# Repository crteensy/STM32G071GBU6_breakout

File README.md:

# STM32G071GBU6_breakout
Breakout board for the STM32G071GBU6

## Partially tested
I've built one of these and measured:

- (unpowered) no shorts
- (unpowered) diode between I/O and ground
- (powered) 3V3 output is fine

Reset was not tested.

I didn't have the exact switch (KMR2) but one with an extra ground tab (KMR2xxG) but you that's not a problem - the ground tab doesn't touch antything.

Flashing a binary with st-flash worked too.

The breakout board was not tested with external circuitry yet.

## Short description

A very simple breakout board for the STM32G071GBU6:

Reset circuitry (pull-up, cap, push button to GND) can be connected to PF2/NRST by closing solder jumper JP1.

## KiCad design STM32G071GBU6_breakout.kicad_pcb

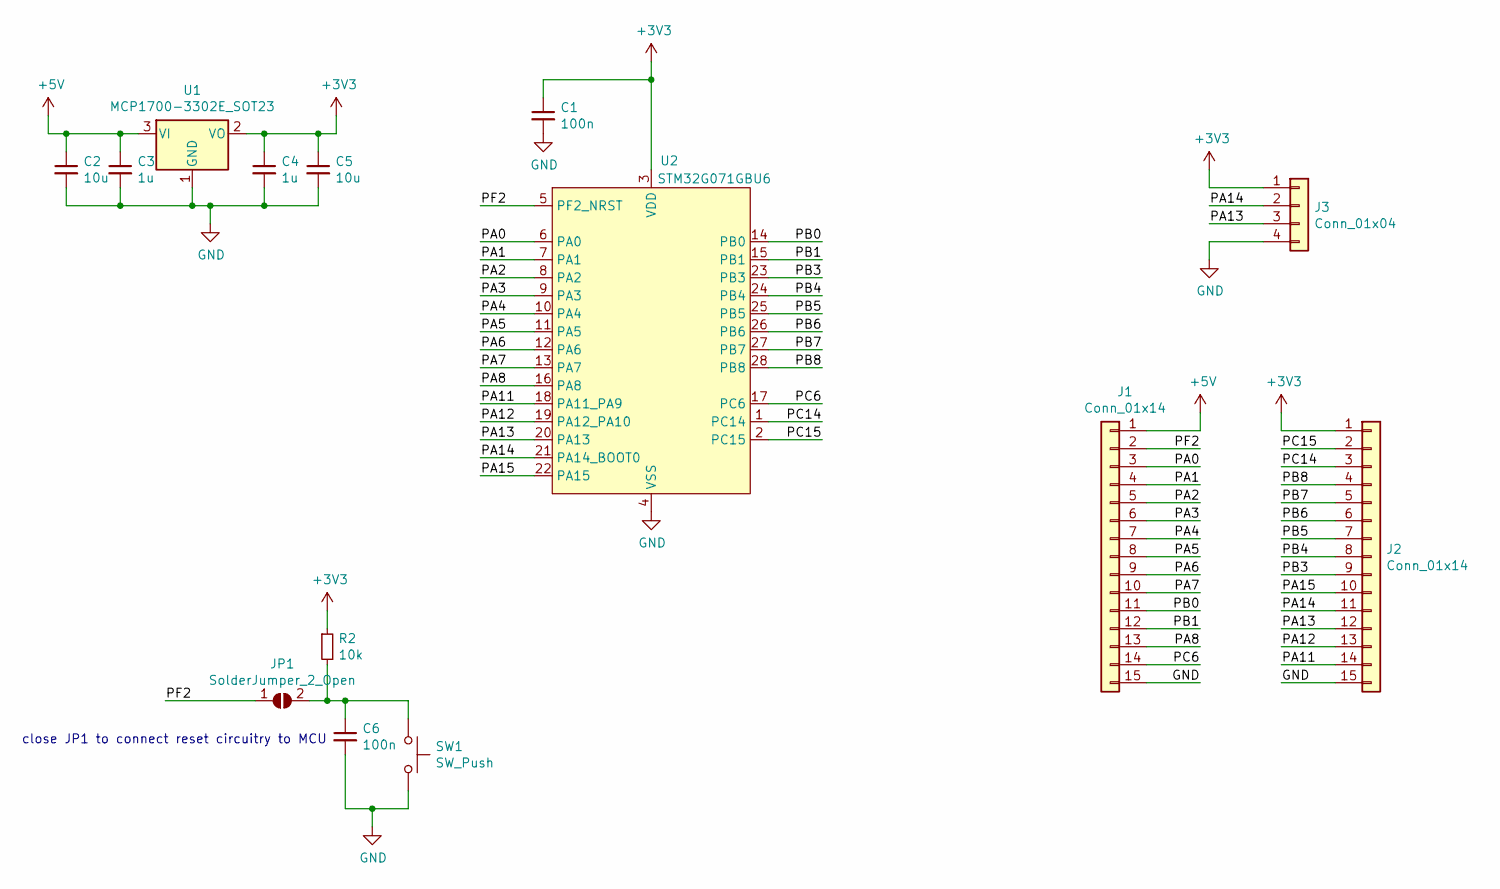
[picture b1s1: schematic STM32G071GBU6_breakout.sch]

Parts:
C1, C6: 100n; C_0603_1608Metric
C2, C5: 10u; C_1206_3216Metric
C3, C4: 1u; C_0603_1608Metric
J1, J2: Conn_01x14; PinHeader_1x15_P2.54mm_Vertical
J3: Conn_01x04; PinHeader_1x04_P2.54mm_Vertical
JP1: SolderJumper_2_Open; SolderJumper-2_P1.3mm_Open_Pad1.0x1.5mm
R2: 10k; R_0603_1608Metric
SW1: SW_Push; SW_Push_1P1T_NO_CK_KMR2
U1: MCP1700-3302E_SOT23; SOT-23
U2: STM32G071GBU6; UFQFPN28

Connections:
+3V3: C1.1, C4.1, C5.1, J2.1, J3.1, R2.1, U1.2 (VO), U2.3 (VDD)
+5V: C2.1, C3.1, J1.1, U1.3 (VI)
/PA0: J1.3, U2.6 (PA0)
/PA1: J1.4, U2.7 (PA1)
/PA2: J1.5, U2.8 (PA2)
/PA3: J1.6, U2.9 (PA3)
/PA4: J1.7, U2.10 (PA4)
/PA5: J1.8, U2.11 (PA5)
/PA6: J1.9, U2.12 (PA6)
/PA7: J1.10, U2.13 (PA7)
/PA8: J1.13, U2.16 (PA8)
/PA11: J2.14, U2.18 (PA11_PA9)
/PA12: J2.13, U2.19 (PA12_PA10)
/PA13: J2.12, J3.3, U2.20 (PA13)
/PA14: J2.11, J3.2, U2.21 (PA14_BOOT0)
/PA15: J2.10, U2.22 (PA15)
/PB0: J1.11, U2.14 (PB0)
/PB1: J1.12, U2.15 (PB1)
/PB3: J2.9, U2.23 (PB3)
/PB4: J2.8, U2.24 (PB4)
/PB5: J2.7, U2.25 (PB5)
/PB6: J2.6, U2.26 (PB6)
/PB7: J2.5, U2.27 (PB7)
/PB8: J2.4, U2.28 (PB8)
/PC6: J1.14, U2.17 (PC6)
/PC14: J2.3, U2.1 (PC14)
/PC15: J2.2, U2.2 (PC15)
/PF2: J1.2, JP1.1 (A), U2.5 (PF2_NRST)
GND: C1.2, C2.2, C3.2, C4.2, C5.2, C6.2, J1.15, J2.15, J3.4, SW1.2, U1.1 (GND), U2.4 (VSS)
unnamed: C6.1, JP1.2 (B), R2.2, SW1.1

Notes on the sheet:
close JP1 to connect reset circuitry to MCU

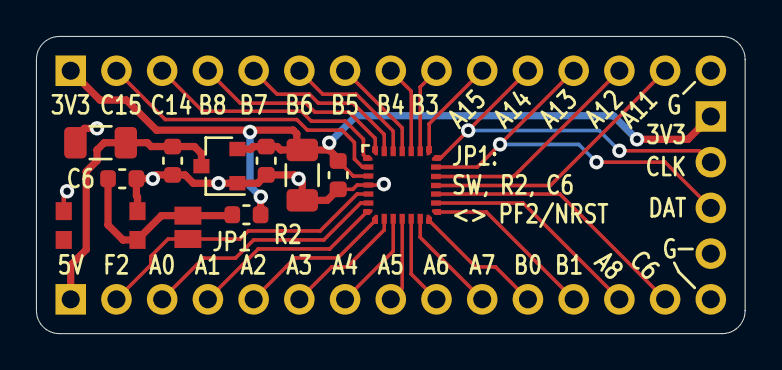
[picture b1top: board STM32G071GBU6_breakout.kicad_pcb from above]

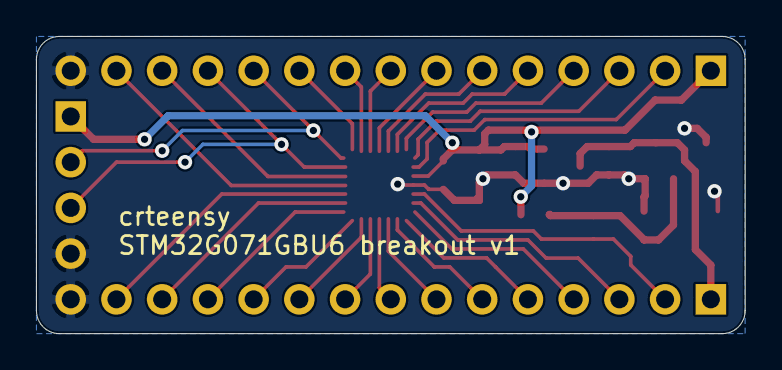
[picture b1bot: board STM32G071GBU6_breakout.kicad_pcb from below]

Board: 2 copper layers, 39.4 x 16.5 mm, 14 parts (2 on the bottom side), 30 nets.

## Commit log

2021-01-28 initial commit, board not tested yet
2021-01-28 change SW to KMR2
2021-02-05 update readme: board partially tested
